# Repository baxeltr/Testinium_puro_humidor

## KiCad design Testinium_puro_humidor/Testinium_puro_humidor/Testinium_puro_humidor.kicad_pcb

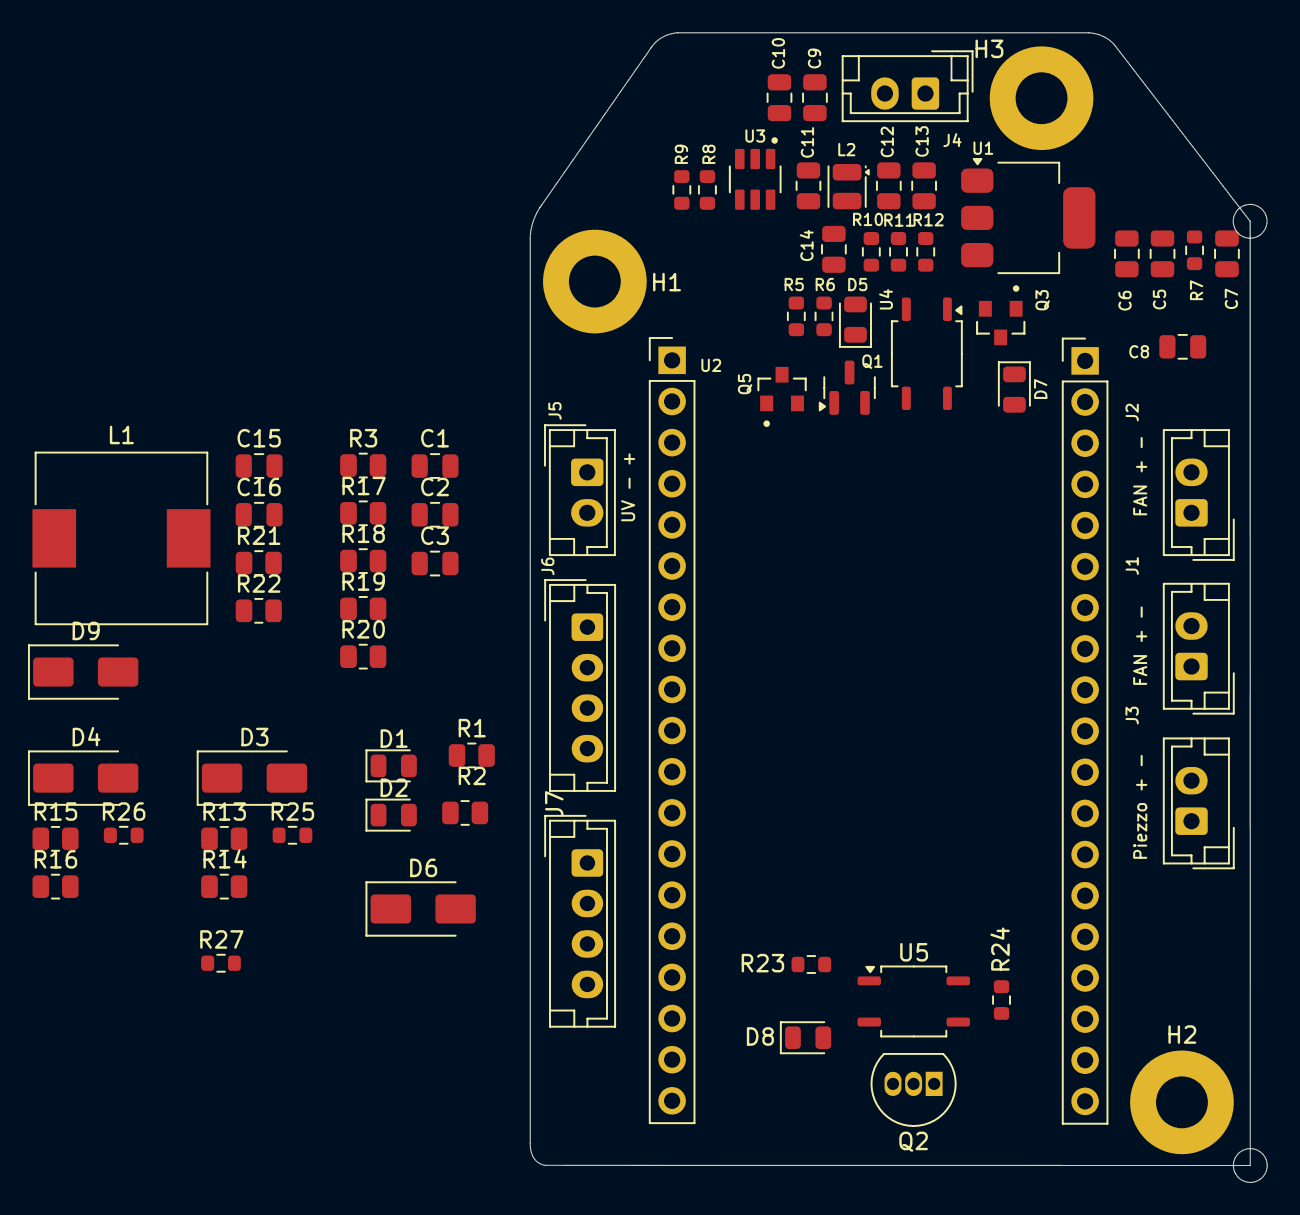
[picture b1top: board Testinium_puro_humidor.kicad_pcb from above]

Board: 2 copper layers, 45.5 x 71.0 mm, 71 parts (0 on the bottom side), 41 nets, no tracks yet.

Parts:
C1: 22uF / 25v; C_0805_2012Metric
C2, C3: 0.1uF / 25v; C_0805_2012Metric
C5, C6, C7, C8, C10, C11: 0.1uF/16V; C_0805_2012Metric
C9: 10uF/16V; C_0805_2012Metric
C12, C13: 22uF/16V; C_0805_2012Metric
C14: 75pF/16V; C_0805_2012Metric
C15, C16: 47nF; C_0805_2012Metric
D1, D5, D7, D8: GreenLed; LED_0805_2012Metric
D2: RedLed; LED_0805_2012Metric
D3, D4, D6, D9: D; D_SMA
H1, H2, H3: MountingHole_Pad_MP; MountingHole_3.2mm_M3_Pad
J1, J2: Conn_01x02_Fan1; JST_EH_B2B-EH-A_1x02_P2.50mm_Vertical
J3: Piezzo; JST_EH_B2B-EH-A_1x02_P2.50mm_Vertical
J4: Power_Conn; JST_EH_B2B-EH-A_1x02_P2.50mm_Vertical
J5: Conn_01x02_UV_LED; JST_EH_B2B-EH-A_1x02_P2.50mm_Vertical
J6: Conn_Sht31; JST_EH_B4B-EH-A_1x04_P2.50mm_Vertical
J7: Conn_Oled; JST_EH_B4B-EH-A_1x04_P2.50mm_Vertical
L1: 100mH; L_10.4x10.4_H4.8
L2: 15uL; L_Coilcraft_0805HQ_2012Metric
Q1: 2N3904; SOT-23
Q2: 2SC5200; TO-92_Inline
Q3, Q5: IRLML6344TRPBF; TRANS_IRLML6344TRPBF
R1, R2: 330R; R_0805_2012Metric
R3: 10k; R_0805_2012Metric
R5, R6, R24: 100R; R_0603_1608Metric
R7: 1R; R_0603_1608Metric
R8: 511kR; R_0603_1608Metric
R9: 105kR; R_0603_1608Metric
R10: 49.9R; R_0603_1608Metric
R11: 100kR; R_0603_1608Metric
R12: 13.3kR; R_0603_1608Metric
R13, R16: 150R; R_0805_2012Metric
R14, R15: 10K; R_0805_2012Metric
R17, R18, R19, R20: 4K7; R_0805_2012Metric
R21: 2K2; R_0805_2012Metric
R22: 4R7; R_0805_2012Metric
R23: 330R; R_0603_1608Metric
R25, R26, R27: 0R; R_0603_1608Metric
U1: LD1117S33TR_SOT223; SOT-223-3_TabPin2
U2: ESP32-DEVKITC-32D; pin_header_esp32
U3: TPS54202DDC; SOT95P280X110-6N
U4, U5: PC817; SOP-4_3.8x4.1mm_P2.54mm

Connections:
3V3: C5.1, C6.1, J7.1, R5.1, R7.1, R23.1, U1.2 (VO)
5V: R25.2, R26.2, R27.1
+3V3: R17.2, R18.2, R19.2, R20.2
/ESP32/EN: C3.1, R3.2, U2.J2-2 (EN)
/ESP32/I2C0_SCL: J7.3, R18.1, U2.J3-13 (IO4)
/ESP32/I2C0_SDA: J7.2, R17.1, U2.J3-14 (IO0)
/ESP32/I2C1_SCL: J6.3, R20.1, U2.J3-18 (SD0)
/ESP32/I2C1_SDA: J6.2, R19.1, U2.J3-17 (SD1)
/FAN1/FAN1_Duty: R13.1, R14.2
/FAN2/FAN2_Duty: R15.2, R16.1
/regulator/5V: C12.2, C13.2, L2.2, R10.2, U1.3 (VI)
Fan1_+: D3.1 (K), J1.1, R25.1
Fan1_-: D3.2 (A), J1.2, Q5.3
Fan2_+: D4.1 (K), J2.1, R26.1
Fan2_-: D4.2 (A), J2.2, Q3.3
unnamed: C14.2, R10.1, R11.2
unnamed: C15.2, C16.2, R21.2, R22.1
unnamed: D1.2 (A), R1.2
unnamed: D2.2 (A), R2.2
unnamed: D5.2 (A), U4.2
unnamed: D8.2 (A), U5.2
unnamed: J6.1, R27.2
unnamed: Q1.2 (B), R6.1
unnamed: Q2.3 (B), R22.2
unnamed: C16.1, L1.1, Q2.1 (E)
unnamed: Q3.1, R16.2
unnamed: Q5.1, R13.2
unnamed: R5.2, U4.1
unnamed: R6.2, U4.3
unnamed: R23.2, U5.1
unnamed: R24.2, U5.3
unnamed: C11.1, U3.6 (BOOT)
unnamed: R8.1, R9.2, U3.5 (EN)
unnamed: C14.1, R11.1, R12.2, U3.4 (FB)
unnamed: C11.2, L2.1, U3.2 (SW)
Piezzo_-: C1.2, C2.2, C3.2, C5.2, C6.2, C7.2, C8.2, C9.2, C10.2, C12.1, C13.1, D1.1 (K), D2.1 (K), D7.1 (K), D9.1 (K), J3.2, J4.1, J6.4, J7.4, L1.2, Q1.1 (E), Q2.2 (C), Q3.2, Q5.2, R9.1, R12.1, R14.1, R15.1, R24.1, U1.1 (GND), U3.1 (GND)
Power: C9.1, C10.1, J4.2, R8.2, U3.3 (VIN)
UV_LED_+: D6.1 (K), D6.2 (A), J5.1, J5.2, Q1.3 (C), U4.4
VDD3: C1.1, C2.1, C7.1, C8.1, D7.2 (A), R3.1, R7.2, U2.J2-1 (3V3)
piezzo_pin1: C15.1, J3.1
piezzo_vcc: D9.2 (A), R21.1, U5.4

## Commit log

2026-03-10 proje olusturuldu
2026-03-10 toplanti taslagi eklendi
2026-03-11 fan , uv led ,regülator devresi eklendi. piezo ve sarj devresi kaldi
2026-03-12 sematik tamamlandi
